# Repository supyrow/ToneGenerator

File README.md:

# ToneGenerator RevB

# ToneGenerator RevA

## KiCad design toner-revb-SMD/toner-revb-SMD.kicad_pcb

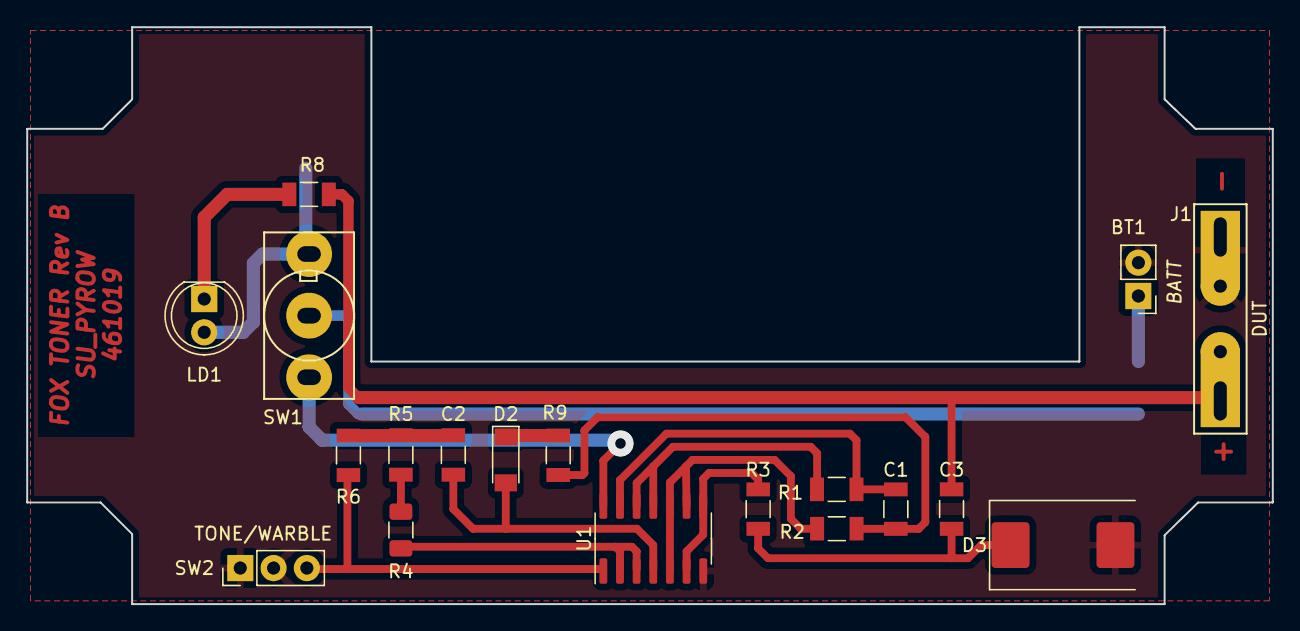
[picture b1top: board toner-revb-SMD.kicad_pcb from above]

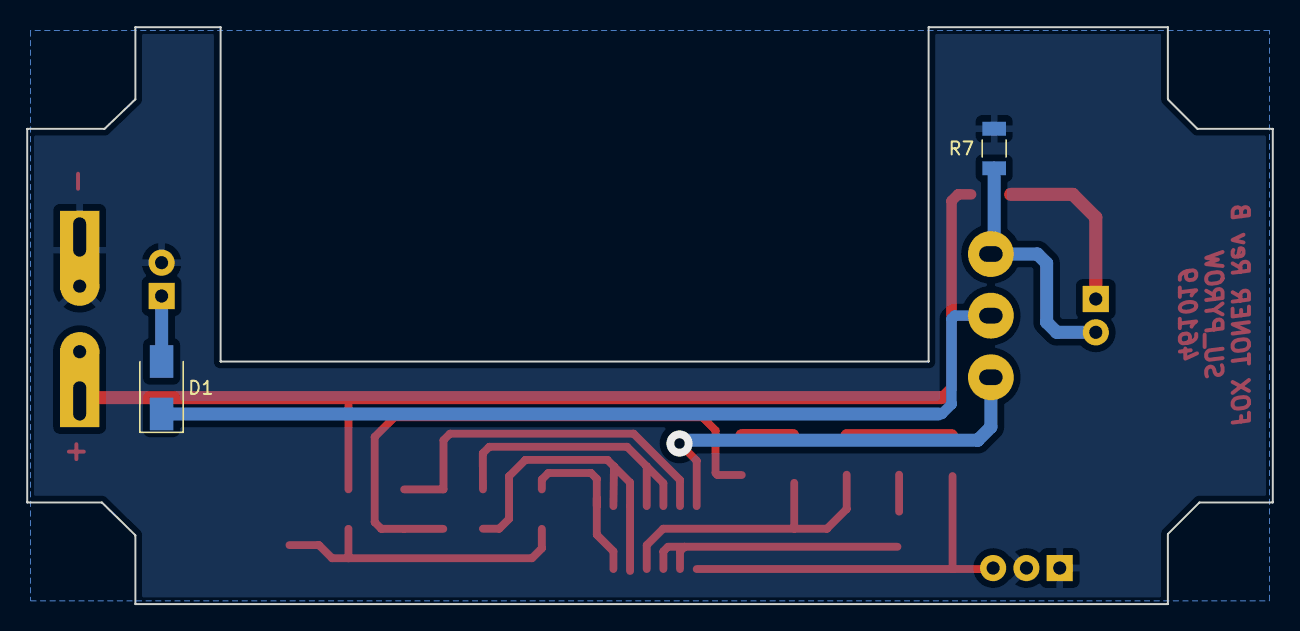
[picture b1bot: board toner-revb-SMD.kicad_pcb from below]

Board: 2 copper layers, 95.0 x 44.0 mm, 21 parts (2 on the bottom side), 19 nets.

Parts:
BT1: BATT; PinHeader_1x02_P2.54mm_Vertical
C1: 1nF @ 100V; C_1206_3216Metric
C2: 100nF @ 50V; C_1206_3216Metric
C3: 100nF @ 250V; C_1206_3216Metric
D1: S1M; D_SMA
D2: LL4148; D_MiniMELF
D3: VP3225K401R300; D_3225_8063Metric
J1: DUT; Connector-blade
LD1: Bi-Color LED; LED_D5.0mm_Clear
R1: 620K; R_1206_3216Metric
R2, R9: 2K2; R_1206_3216Metric
R3: 100R; R_1206_3216Metric
R4, R5: 1M; R_1206_3216Metric
R6, R7: 21K; R_1206_3216Metric
R8: 22K; R_1206_3216Metric
SW1: SPDT; SWITCH-toggle-100SP3T1B1M2QEH
SW2: TONE/WARBLE; PinHeader_1x03_P2.54mm_Vertical
U1: 4069; SOIC-14_3.9x8.7mm_P1.27mm

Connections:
+9V: BT1.1 (+), D1.2 (A)
/CONT: LD1.2 (AK), R7.1, SW1.3 (C)
/TONE: SW1.1 (A), U1.14 (VDD)
GND: BT1.2 (-), D3.2 (A2), J1.2, R7.2, SW2.1 (A), SW2.2 (B), U1.7 (VSS)
unnamed: C1.1, R1.1, U1.13
unnamed: C1.2, R2.2, R9.2
unnamed: C2.1, R5.1, R6.2
unnamed: C2.2, D2.2 (A), U1.4
unnamed: C3.1, D3.1 (A1), R3.1
unnamed: C3.2, J1.1, R8.1
unnamed: D1.1 (K), SW1.2 (B)
unnamed: D2.1 (K), R9.1
unnamed: LD1.1 (KA), R8.2
unnamed: R1.2, U1.11, U1.12
unnamed: R2.1, U1.5, U1.9, U1.10
unnamed: R3.2, U1.6, U1.8
unnamed: R4.1, R5.2
unnamed: R4.2, U1.2, U1.3
unnamed: R6.1, SW2.3 (C), U1.1

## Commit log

2021-05-20 Added initial design files for RevA
2021-05-20 Added RevB SMD version
2021-05-20 Adjusted some directory structure
